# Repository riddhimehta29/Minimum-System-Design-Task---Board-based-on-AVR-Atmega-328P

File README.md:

Minimum System Design Task - Board based on AVR Atmega 328P using KiCad for IPD task 01

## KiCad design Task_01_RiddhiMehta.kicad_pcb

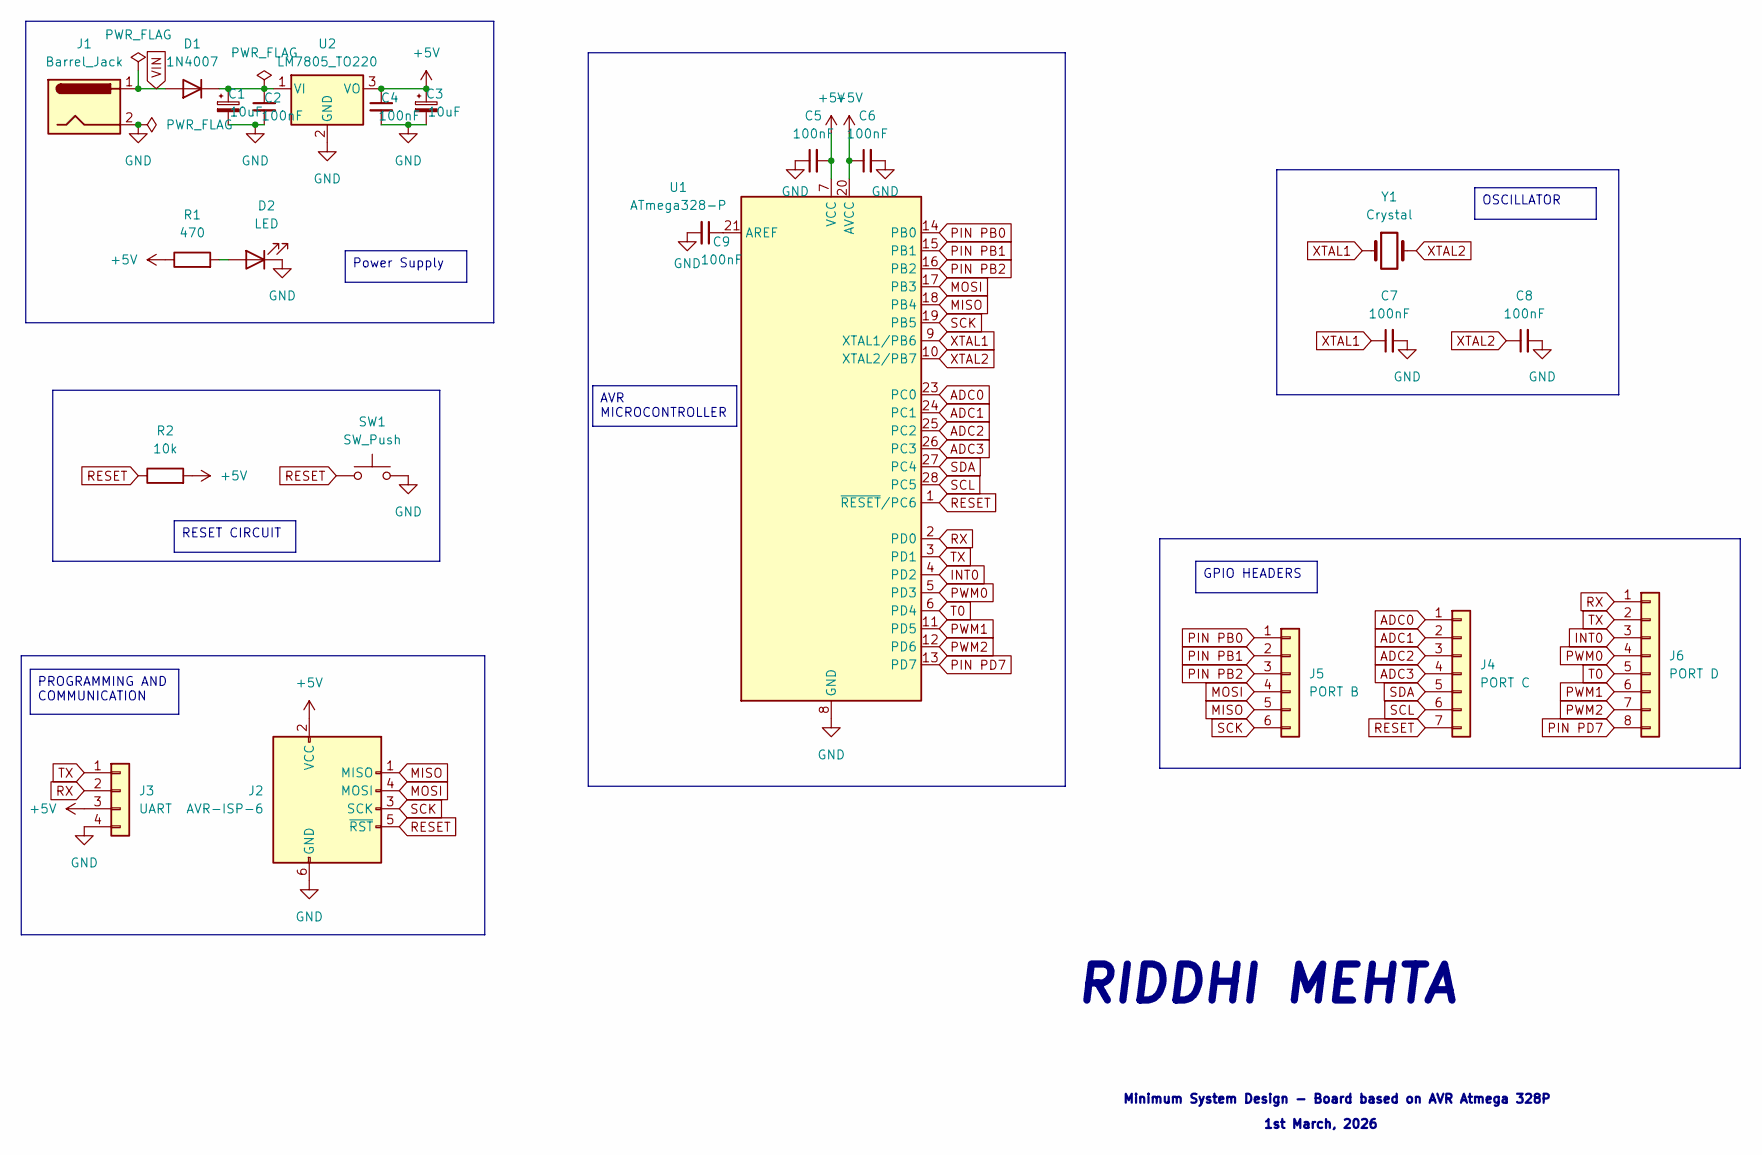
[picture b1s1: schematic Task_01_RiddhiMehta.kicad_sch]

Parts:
C1, C3: 10uF; CP_Radial_D6.3mm_P2.50mm
C2, C4, C5, C6, C7, C8, C9: 100nF; C_Disc_D5.0mm_W2.5mm_P2.50mm
D1: 1N4007; D_DO-41_SOD81_P10.16mm_Horizontal
D2: LED; LED_D5.0mm
J1: Barrel_Jack; BarrelJack_Horizontal
J2: AVR-ISP-6; PinHeader_1x06_P2.54mm_Horizontal
J3: UART; PinHeader_1x04_P2.54mm_Horizontal
J4: PORT C; PinHeader_1x07_P2.54mm_Vertical
J5: PORT B; PinHeader_1x06_P2.54mm_Vertical
J6: PORT D; PinHeader_1x08_P2.54mm_Vertical
R1: 470; R_Axial_DIN0207_L6.3mm_D2.5mm_P7.62mm_Horizontal
R2: 10k; R_Axial_DIN0207_L6.3mm_D2.5mm_P7.62mm_Horizontal
SW1: SW_Push; SW_PUSH_6mm
U1: ATmega328-P; DIP-28_W7.62mm
U2: LM7805_TO220; TO-220-3_Vertical
Y1: Crystal; Crystal_HC49-U_Vertical

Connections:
+5V: C3.1, C4.1, C5.2, C6.1, J2.2 (VCC), J3.3, R1.1, R2.2, U1.7 (VCC), U1.20 (AVCC), U2.3 (VO)
ADC0: J4.1, U1.23 (PC0)
ADC1: J4.2, U1.24 (PC1)
ADC2: J4.3, U1.25 (PC2)
ADC3: J4.4, U1.26 (PC3)
GND: C1.2, C2.2, C3.2, C4.2, C5.1, C6.2, C7.2, C8.2, C9.2, D2.1 (K), J1.2, J2.6 (GND), J3.4, SW1.2, U1.8 (GND), U1.22 (GND), U2.2 (GND)
INT0: J6.3, U1.4 (PD2)
MISO: J2.1 (MISO), J5.5, U1.18 (PB4)
MOSI: J2.4 (MOSI), J5.4, U1.17 (PB3)
unnamed: C1.1, C2.1, D1.1 (K), U2.1 (VI)
unnamed: D2.2 (A), R1.2
unnamed: C9.1, U1.21 (AREF)
PIN PB0: J5.1, U1.14 (PB0)
PIN PB1: J5.2, U1.15 (PB1)
PIN PB2: J5.3, U1.16 (PB2)
PIN PD7: J6.8, U1.13 (PD7)
PWM0: J6.4, U1.5 (PD3)
PWM1: J6.6, U1.11 (PD5)
PWM2: J6.7, U1.12 (PD6)
RESET: J2.5 (~RST), J4.7, R2.1, SW1.1, U1.1 (~RESET/PC6)
RX: J3.2, J6.1, U1.2 (PD0)
SCK: J2.3 (SCK), J5.6, U1.19 (PB5)
SCL: J4.6, U1.28 (PC5)
SDA: J4.5, U1.27 (PC4)
T0: J6.5, U1.6 (PD4)
TX: J3.1, J6.2, U1.3 (PD1)
VIN: D1.2 (A), J1.1
XTAL1: C7.1, U1.9 (XTAL1/PB6), Y1.1
XTAL2: C8.1, U1.10 (XTAL2/PB7), Y1.2

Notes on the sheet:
1st March, 2026
RIDDHI MEHTA
Minimum System Design - Board based on AVR Atmega 328P
RESET CIRCUIT
GPIO HEADERS
AVR MICROCONTROLLER
OSCILLATOR
PROGRAMMING AND COMMUNICATION
Power Supply

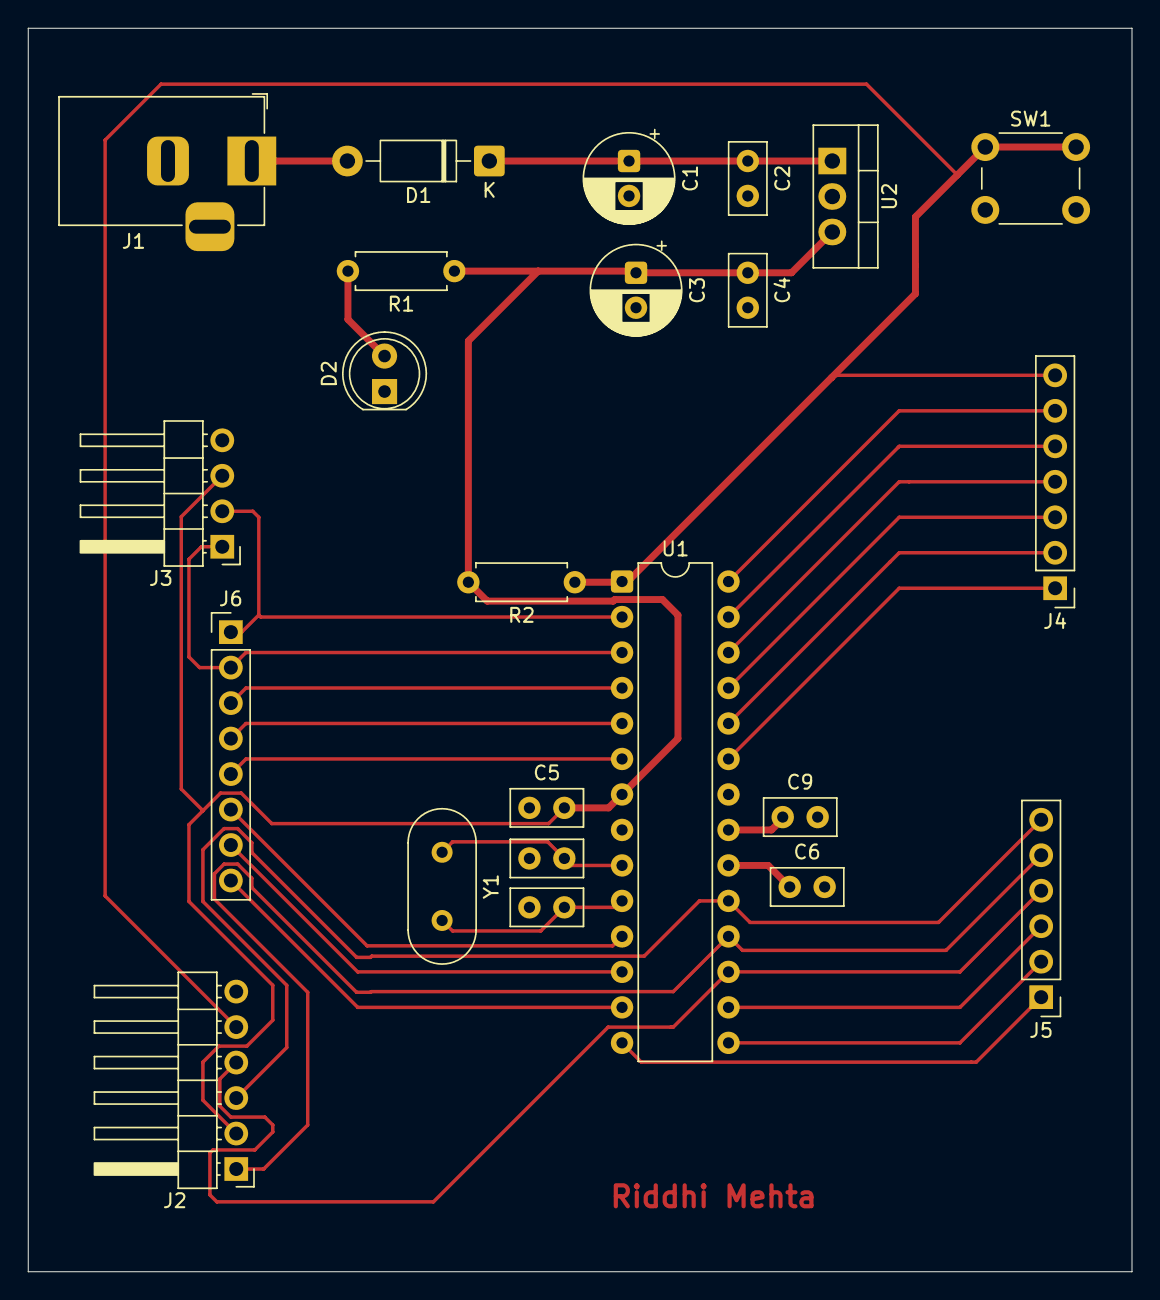
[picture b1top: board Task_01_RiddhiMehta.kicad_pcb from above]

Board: 2 copper layers, 79.0 x 89.0 mm, 23 parts (0 on the bottom side), 29 nets.
